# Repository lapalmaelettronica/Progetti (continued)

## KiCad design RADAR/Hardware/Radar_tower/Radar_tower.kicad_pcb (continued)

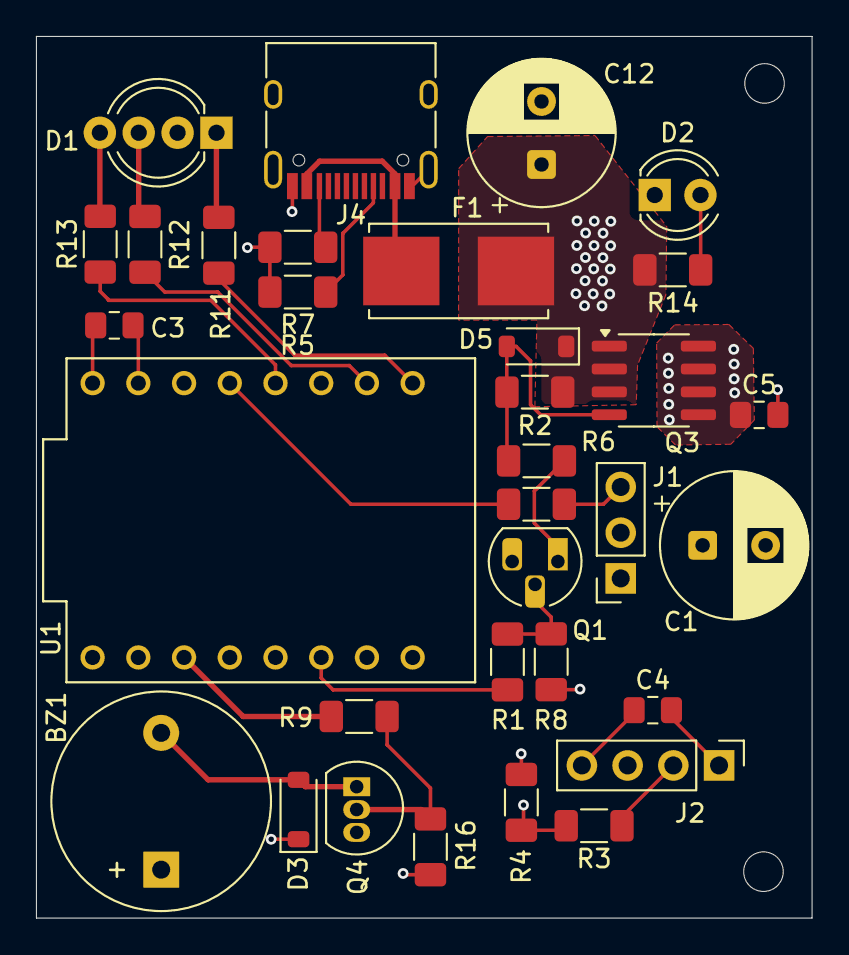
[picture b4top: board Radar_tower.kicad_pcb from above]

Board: 4 copper layers, 43.1 x 49.0 mm, 35 parts (0 on the bottom side), 25 nets.

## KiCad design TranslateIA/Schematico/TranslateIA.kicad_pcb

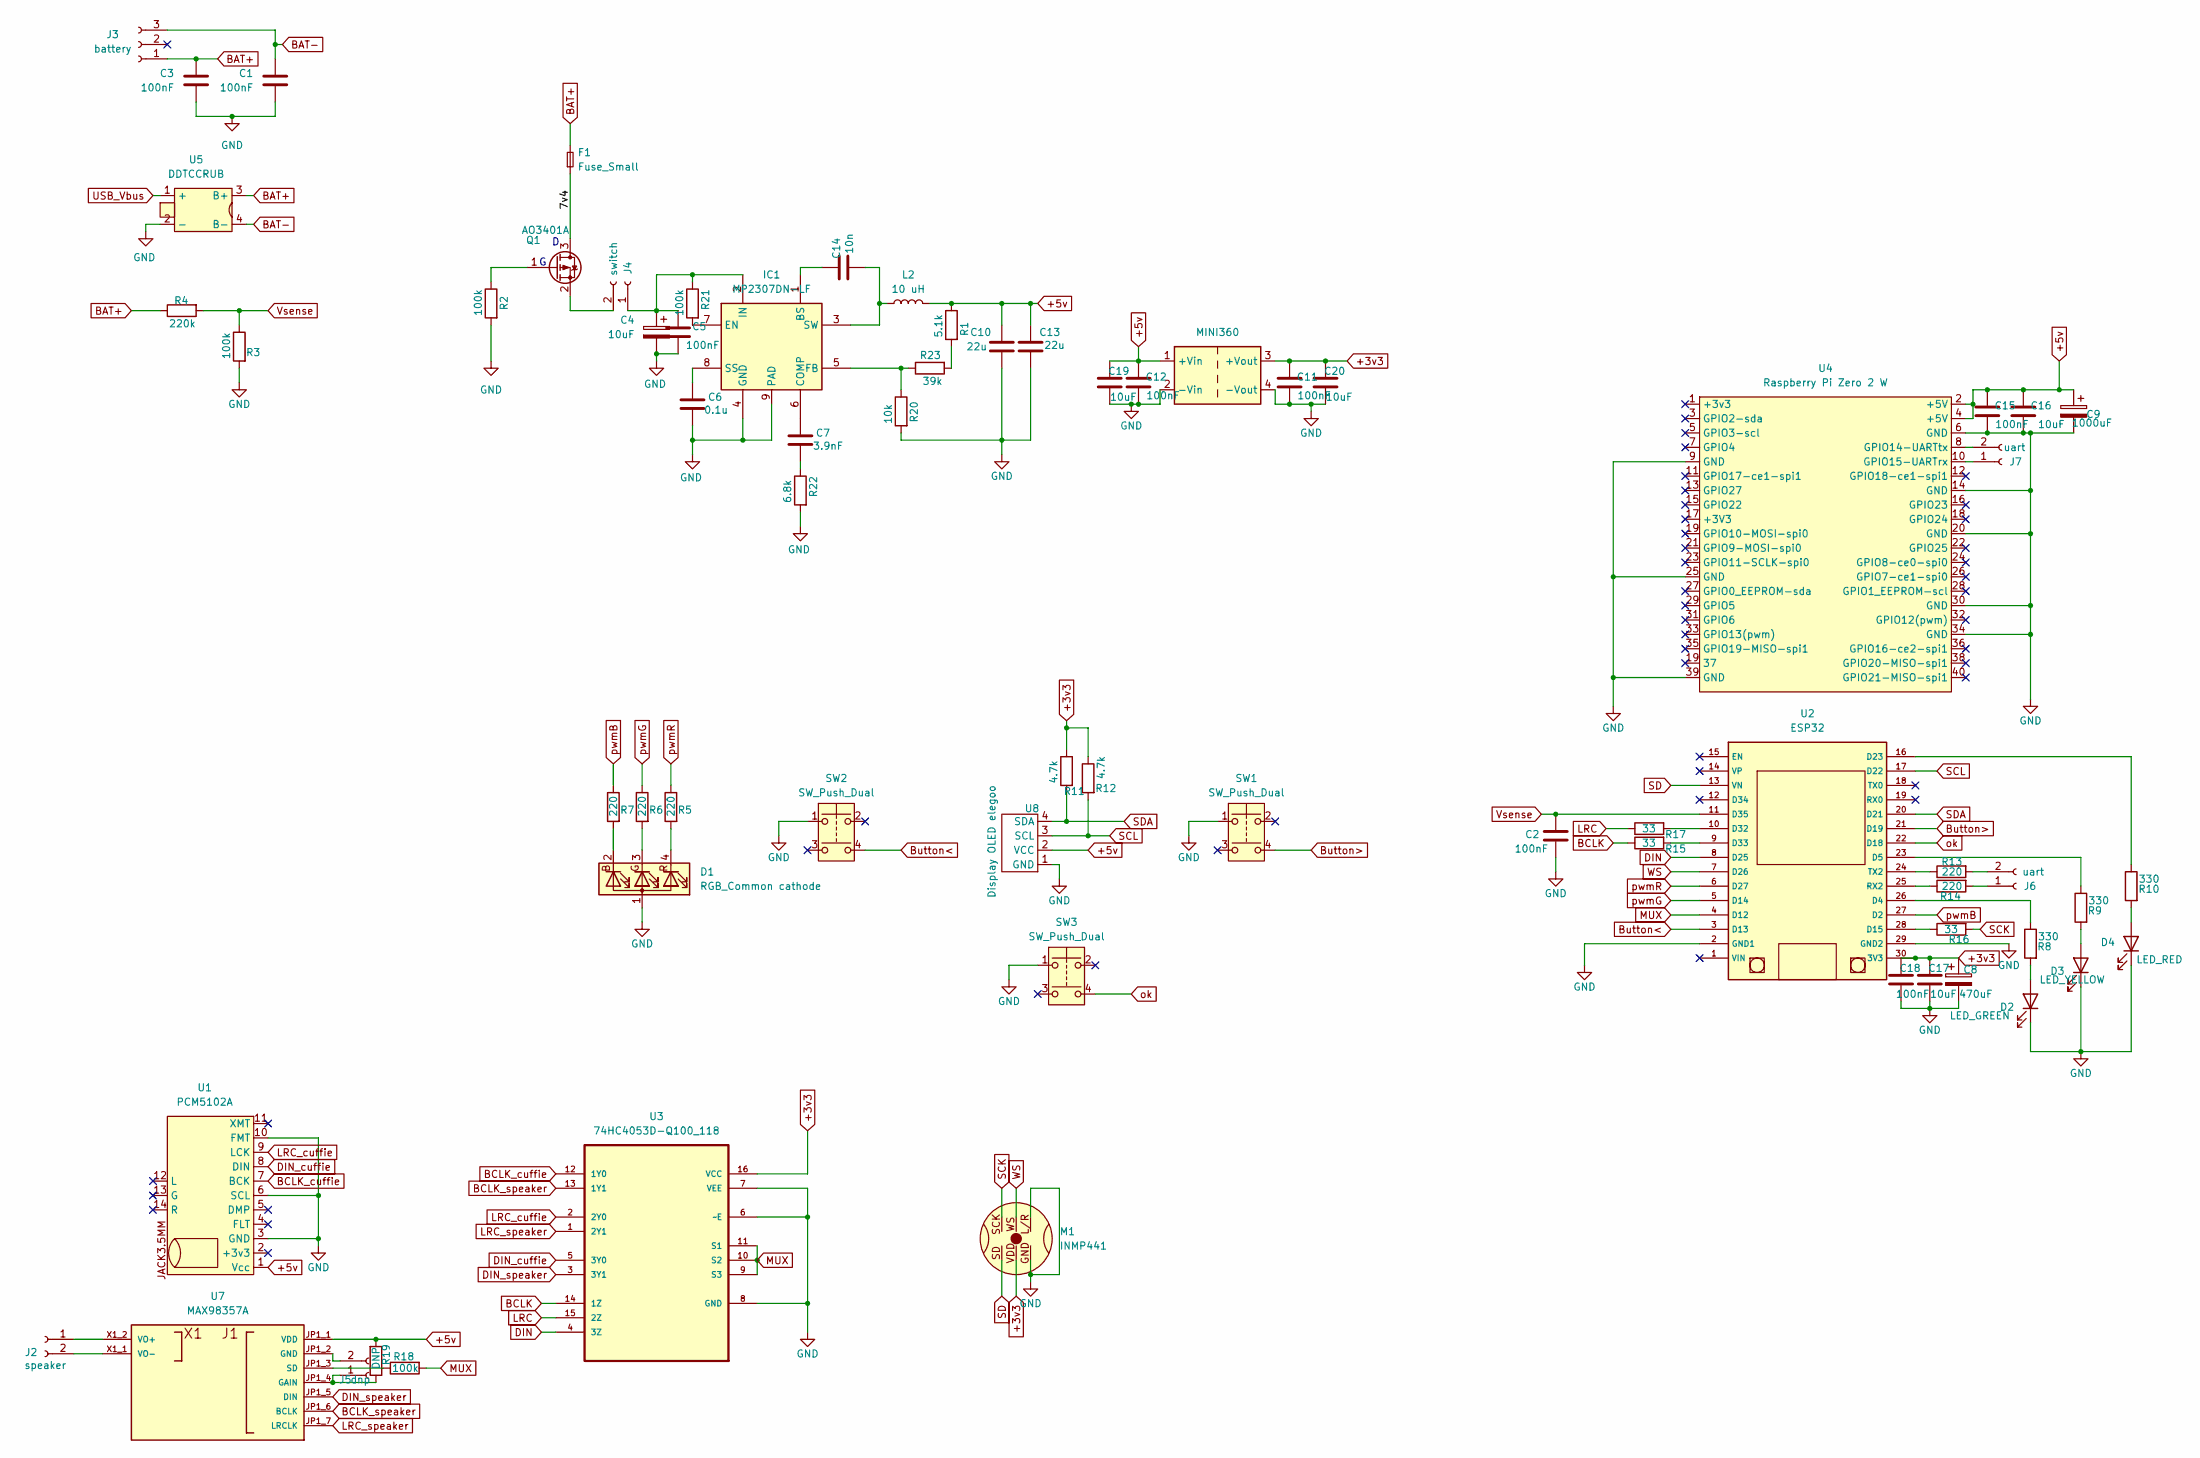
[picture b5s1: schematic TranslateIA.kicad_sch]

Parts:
C1, C2, C3, C5, C11, C12, C15, C18: 100nF; C_0805_2012Metric_Pad1.18x1.45mm_HandSolder
C4, C16, C17, C19, C20: 10uF; C_0805_2012Metric_Pad1.18x1.45mm_HandSolder
C6: 0.1u; C_Disc_D4.3mm_W1.9mm_P5.00mm
C7: 3.9nF; C_Disc_D4.3mm_W1.9mm_P5.00mm
C8: 470uF; CP_Radial_D5.0mm_P2.00mm
C9: 1000uF; CP_Radial_D5.0mm_P2.00mm
C10, C13: 22u; C_Disc_D4.3mm_W1.9mm_P5.00mm
C14: 10n; C_0805_2012Metric_Pad1.18x1.45mm_HandSolder
D1: RGB_Common cathode; LED_D5.0mm-4_RGB_Wide_Pins
D2: LED_GREEN; LED_D4.0mm
D3: LED_YELLOW; LED_D4.0mm
D4: LED_RED; LED_D4.0mm
F1: Fuse_Small; Fuseholder_Littelfuse_Nano2_154x
IC1: MP2307DN-LF; MP2307DNLF; Mouser Part Number 946-MP2307DNLF
J2: speaker; JST_PH_B2B-PH-K_1x02_P2.00mm_Vertical
J3: battery; JST_PH_B3B-PH-K_1x03_P2.00mm_Vertical
J4: switch; Molex_KK-254_AE-6410-02A_1x02_P2.54mm_Vertical
J5: dnp; Molex_KK-254_AE-6410-02A_1x02_P2.54mm_Vertical
J6, J7: uart; Molex_KK-254_AE-6410-02A_1x02_P2.54mm_Vertical
L2: 10 uH; CDRH127
M1: INMP441
Q1: AO3401A; SOT-23
R1: 5.1k; R_1206_3216Metric_Pad1.30x1.75mm_HandSolder
R2, R3, R18, R21: 100k; R_1206_3216Metric_Pad1.30x1.75mm_HandSolder
R4: 220k; R_1206_3216Metric_Pad1.30x1.75mm_HandSolder
R5, R6, R7, R13, R14: 220; R_1206_3216Metric_Pad1.30x1.75mm_HandSolder
R8, R9, R10: 330; R_1206_3216Metric_Pad1.30x1.75mm_HandSolder
R11, R12: 4.7k; R_1206_3216Metric_Pad1.30x1.75mm_HandSolder
R15, R16, R17: 33; R_1206_3216Metric_Pad1.30x1.75mm_HandSolder
R19: DNP; R_1206_3216Metric_Pad1.30x1.75mm_HandSolder
R20: 10k; R_1206_3216Metric_Pad1.30x1.75mm_HandSolder
R22: 6.8k; R_1206_3216Metric_Pad1.30x1.75mm_HandSolder
R23: 39k; R_1206_3216Metric_Pad1.30x1.75mm_HandSolder
SW1, SW2, SW3: SW_Push_Dual; Push_E-Switch_KS01Q01
U1: PCM5102A
U2: ESP32
U3: 74HC4053D-Q100_118; 74HC4053D-SOIC16; MPN 74HC4053D-Q100,118
U4: Raspberry Pi Zero 2 W; Raspberry_Pi_Zero_Socketed_THT_FaceDown_MountingHoles
U5: DDTCCRUB; DDTCCRUB lithium battery charger
U6: MINI360; Mini360
U7: MAX98357A; PARTREV A
U8: Display OLED elegoo; Display OLED mini Elegoo

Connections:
+3v3: C8.1, C11.1, C17.1, C18.1, C20.1, M1.VDD, R11.1, R12.1, U2.30 (3V3), U3.16 (VCC), U6.3 (+Vout)
+5v: C9.1, C10.1, C12.1, C13.1, C15.1, C16.1, C19.1, L2.2, R1.1, R19.2, U1.1 (Vcc), U4.2 (+5V), U4.4 (+5V), U6.1 (+Vin), U7.JP1_1 (VDD), U8.2 (VCC)
/7v4: F1.1, Q1.3 (D)
BAT+: C3.1, F1.2, J3.1, R4.1, U5.3 (B+)
BAT-: C1.1, J3.3, U5.4 (B-)
BCLK: R15.1, U3.14 (1Z)
BCLK_cuffie: U1.7 (BCK), U3.12 (1Y0)
BCLK_speaker: U3.13 (1Y1), U7.JP1_6 (BCLK)
Button<: SW2.4, U2.3 (D13)
Button>: SW1.4, U2.21 (D19)
DIN: U2.8 (D25), U3.4 (3Z)
DIN_cuffie: U1.8 (DIN), U3.5 (3Y0)
DIN_speaker: U3.3 (3Y1), U7.JP1_5 (DIN)
GND: C1.2, C2.2, C3.2, C4.2, C5.2, C6.2, C8.2, C9.2, C10.2, C11.2, C12.2, C13.2, C15.2, C16.2, C17.2, C18.2, C19.2, C20.2, D1.1 (A), D2.1 (K), D3.1 (K), D4.1 (K), IC1.4 (GND), IC1.9 (PAD), M1.GND, M1.L/R, R2.2, R3.2, R20.2, R22.2, SW1.1, SW2.1, SW3.1, U1.3 (GND), U1.6 (SCL), U1.10 (FMT), U2.2 (GND1), U2.29 (GND2), U3.6 (~E), U3.7 (VEE), U3.8 (GND), U4.6 (GND), U4.9 (GND), U4.14 (GND), U4.20 (GND), U4.25 (GND), U4.30 (GND), U4.34 (GND), U4.39 (GND), U5.2 (-), U6.2 (-Vin), U6.4 (-Vout), U8.1 (GND)
LRC: R17.1, U3.15 (2Z)
LRC_cuffie: U1.9 (LCK), U3.2 (2Y0)
LRC_speaker: U3.1 (2Y1), U7.JP1_7 (LRCLK)
MUX: R18.2, U2.4 (D12), U3.9 (S3), U3.10 (S2), U3.11 (S1)
unnamed: C7.2, R22.1
unnamed: D1.2 (BK), R7.2
unnamed: D1.3 (GK), R6.2
unnamed: D1.4 (RK), R5.2
unnamed: D2.2 (A), R8.2
unnamed: D3.2 (A), R9.2
unnamed: D4.2 (A), R10.2
unnamed: C14.1, IC1.1 (BS)
unnamed: C7.1, IC1.6 (COMP)
unnamed: IC1.7 (EN), R21.2
unnamed: IC1.5 (FB), R20.1, R23.1
unnamed: C4.1, C5.1, IC1.2 (IN), J4.1, R21.1
unnamed: C6.1, IC1.8 (SS)
unnamed: C14.2, IC1.3 (SW), L2.1
unnamed: J2.1, U7.X1_2 (VO+)
unnamed: J2.2, U7.X1_1 (VO-)
unnamed: J4.2, Q1.2 (S)
unnamed: J5.1, R19.1, U7.JP1_4 (GAIN)
unnamed: J5.2, U7.JP1_2 (GND)
unnamed: J6.1, R14.2
unnamed: J6.2, R13.2
unnamed: J7.1, U4.10 (GPIO15-UARTrx)
unnamed: J7.2, U4.8 (GPIO14-UARTtx)
unnamed: Q1.1 (G), R2.1
unnamed: R1.2, R23.2
unnamed: R8.1, U2.26 (D4)
unnamed: R9.1, U2.23 (D5)
unnamed: R16.1, U2.28 (D15)
unnamed: R10.1, U2.16 (D23)
unnamed: R17.2, U2.10 (D32)
unnamed: R15.2, U2.9 (D33)
unnamed: R14.1, U2.25 (RX2)
unnamed: R13.1, U2.24 (TX2)
unnamed: R18.1, U7.JP1_3 (SD)
SCK: M1.SCK, R16.2
SCL: R12.2, U2.17 (D22), U8.3 (SCL)
SD: M1.SD, U2.13 (VN)
SDA: R11.2, U2.20 (D21), U8.4 (SDA)
USB_Vbus: U5.1 (+)
Vsense: C2.1, R3.1, R4.2, U2.11 (D35)
WS: M1.WS, U2.7 (D26)
ok: SW3.4, U2.22 (D18)
pwmB: R7.1, U2.27 (D2)
pwmG: R6.1, U2.5 (D14)
pwmR: R5.1, U2.6 (D27)

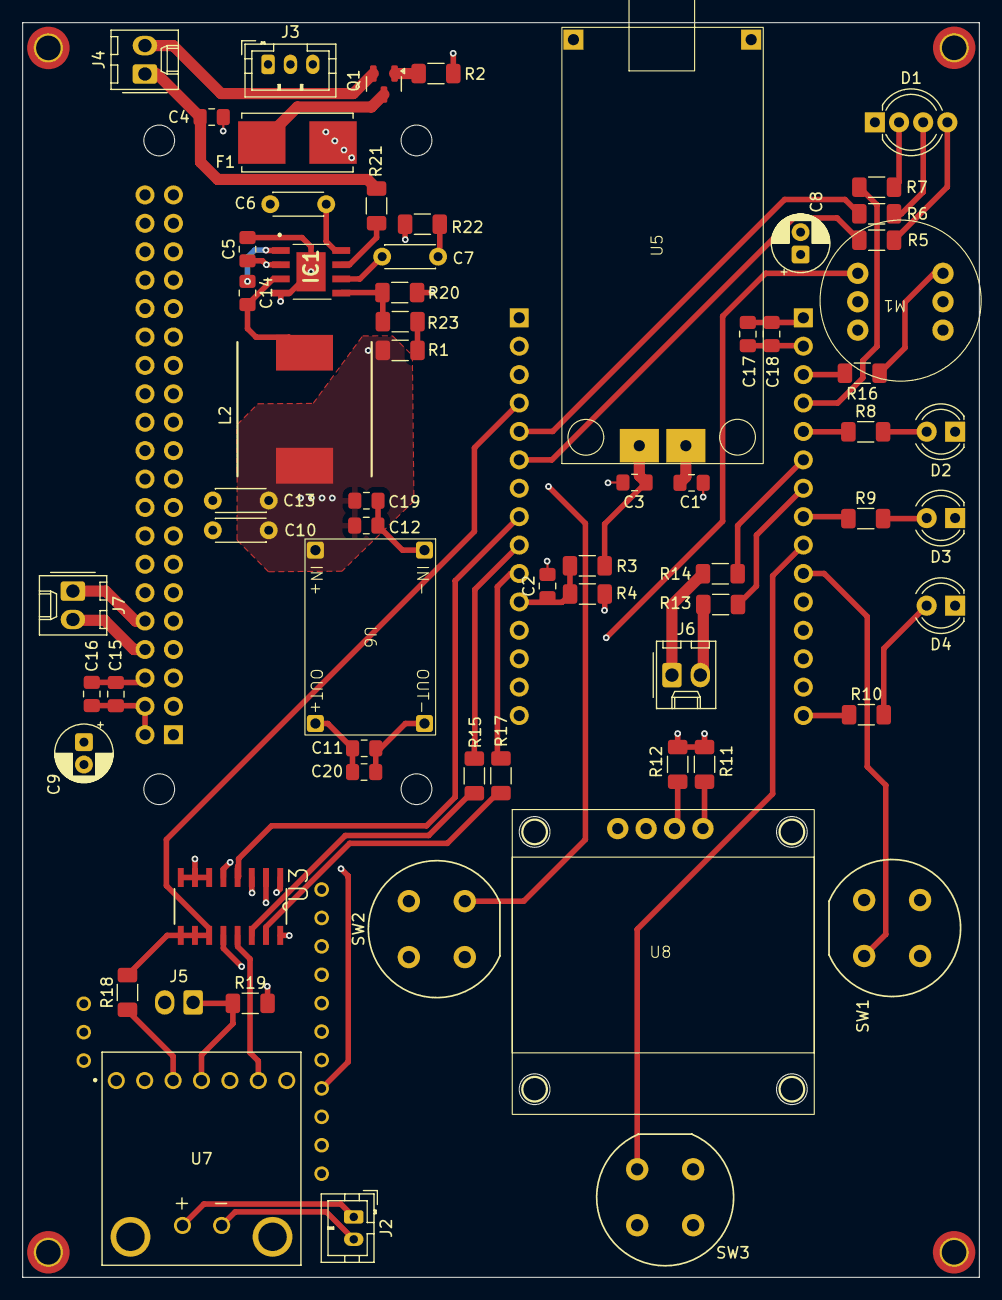
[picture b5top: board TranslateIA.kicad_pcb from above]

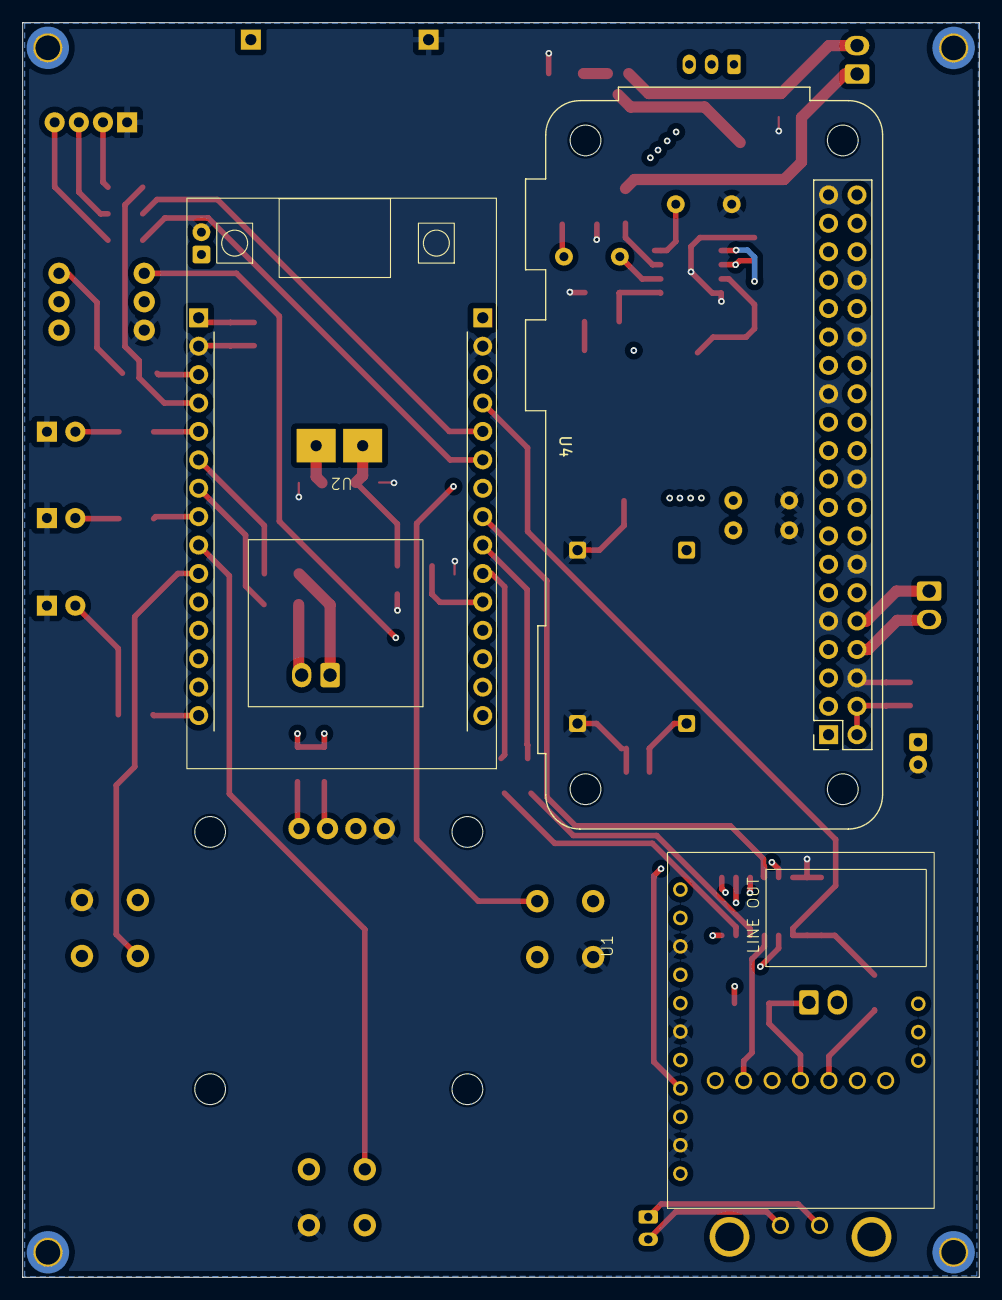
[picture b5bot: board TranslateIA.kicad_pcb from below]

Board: 4 copper layers, 85.5 x 112.2 mm, 69 parts (3 on the bottom side), 62 nets.

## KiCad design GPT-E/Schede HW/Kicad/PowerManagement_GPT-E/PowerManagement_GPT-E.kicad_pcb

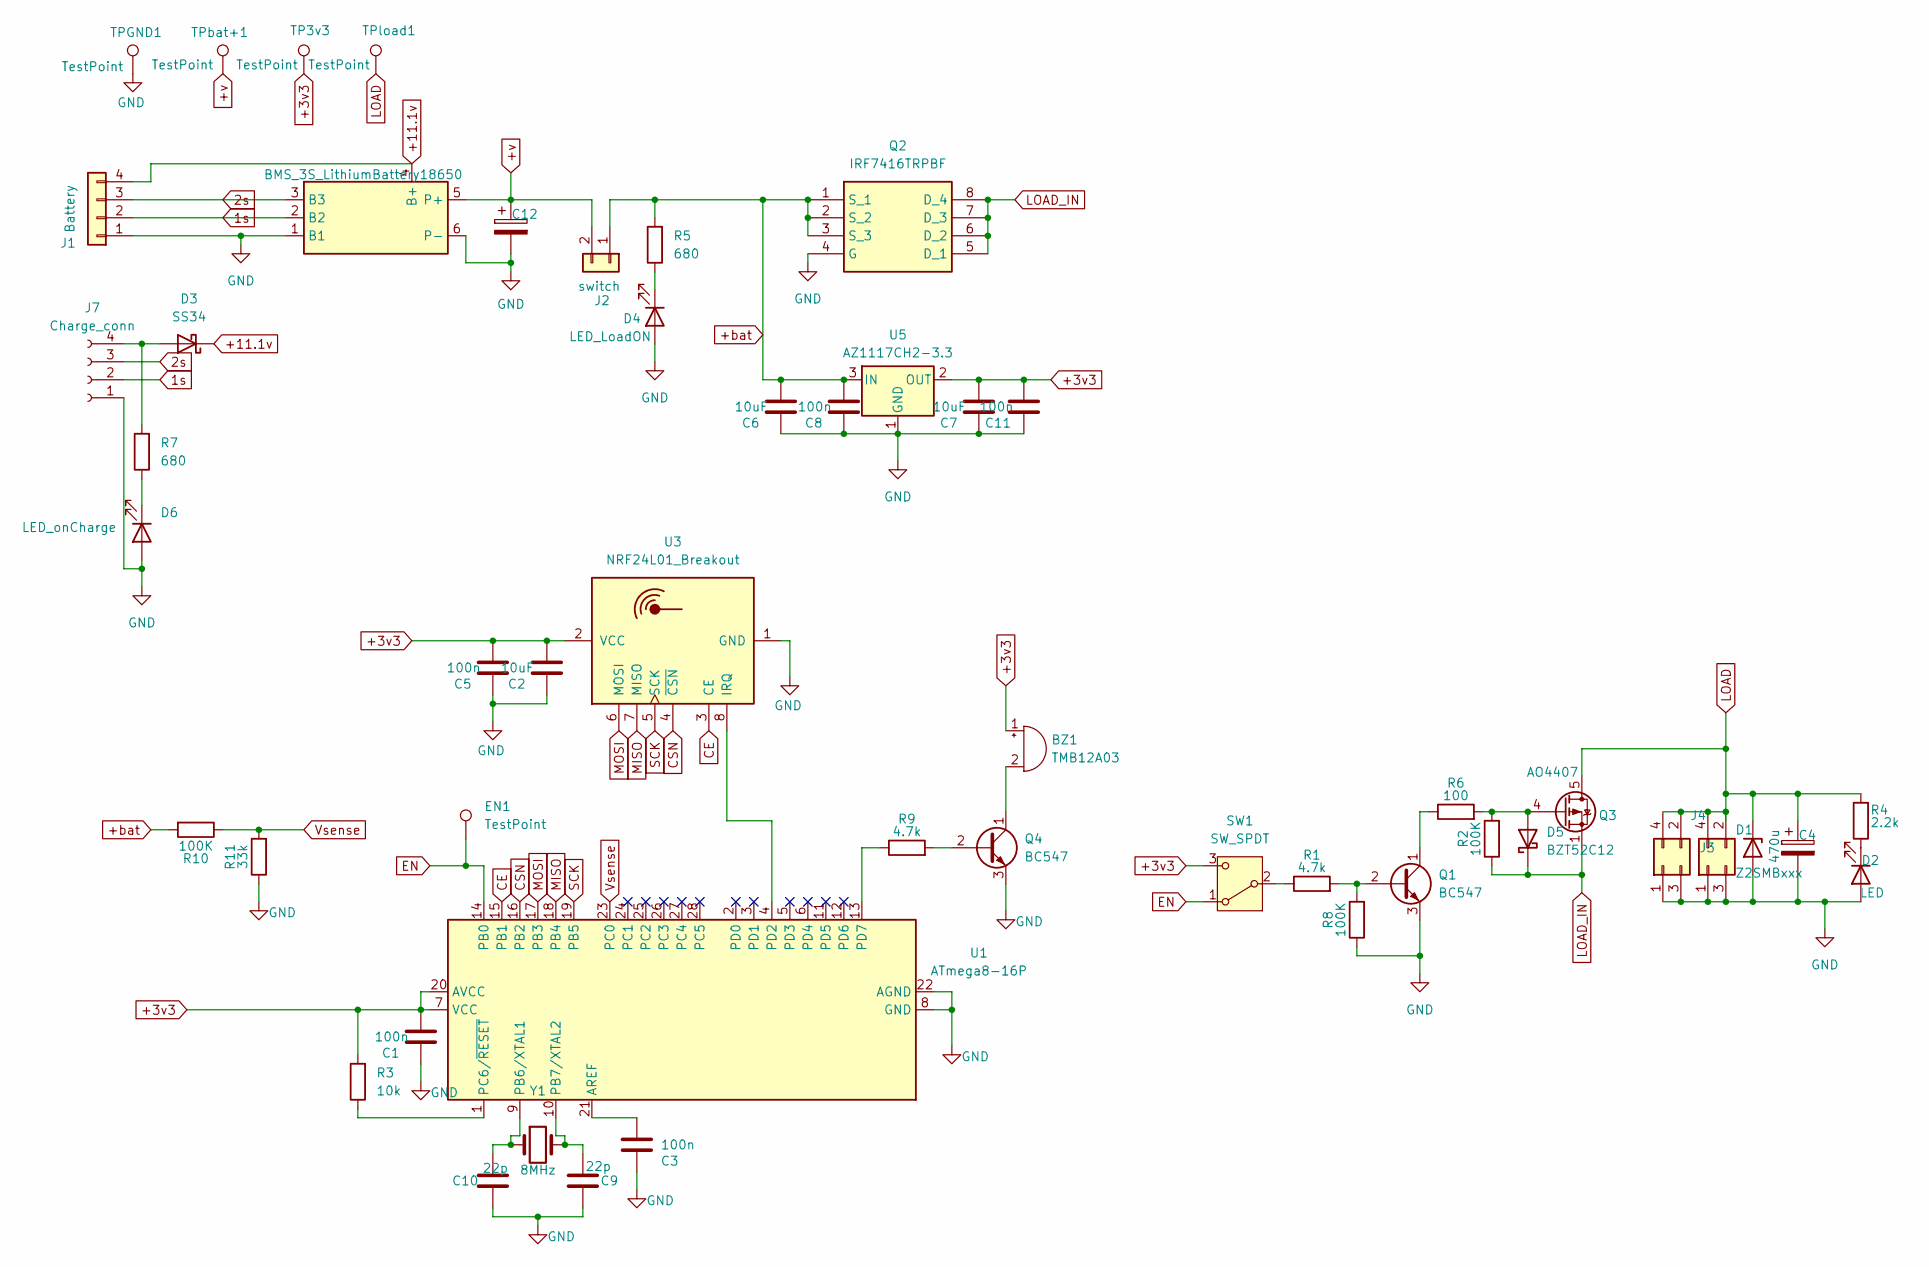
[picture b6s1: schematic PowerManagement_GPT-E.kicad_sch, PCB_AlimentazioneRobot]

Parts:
BZ1: TMB12A03; Buzzer_12x9.5RM7.6
C1, C3, C5, C8, C11: 100n; C_0805_2012Metric_Pad1.18x1.45mm_HandSolder
C2, C6, C7: 10uF; C_0805_2012Metric_Pad1.18x1.45mm_HandSolder
C4, C12: 470u; CP_Radial_D8.0mm_P3.50mm
C9, C10: 22p; C_0805_2012Metric_Pad1.18x1.45mm_HandSolder
D1: Z2SMBxxx; D_SMB_Handsoldering
D2: LED; LED_D4.0mm
D3: SS34; D_SMA_Handsoldering
D4: LED_LoadON; LED_D4.0mm
D5: BZT52C12; D_SOD-123
D6: LED_onCharge; LED_D4.0mm
EN1: TestPoint; TestPoint_Pad_2.0x2.0mm
J1: Battery; FanPinHeader_1x04_P2.54mm_Vertical
J2: switch; Molex_KK-254_AE-6410-02A_1x02_P2.54mm_Vertical
J3: Conn_02x02_Counter_Clockwise; Molex_Micro-Fit_3.0_43045-0412_2x02_P3.00mm_Vertical
J4: Conn_02x02_Counter_Clockwise; Molex_Micro-Fit_3.0_43045-0400_2x02_P3.00mm_Horizontal
J7: Charge_conn; Samtec_UMPS-04-XX.X-X-V-S_1x04_P2.0mm_Socket
Q1, Q4: BC547; TO-92L_Inline
Q2: IRF7416TRPBF; SOIC-8; Mouser Part Number 942-IRF7416TRPBF
Q3: AO4407; SOIC-8_3.9x4.9mm_P1.27mm
R1, R9: 4.7k; R_1206_3216Metric_Pad1.30x1.75mm_HandSolder
R2, R8: 100K; R_1206_3216Metric_Pad1.30x1.75mm_HandSolder
R3: 10k; R_Axial_DIN0204_L3.6mm_D1.6mm_P5.08mm_Horizontal
R4: 2.2k; R_Axial_DIN0204_L3.6mm_D1.6mm_P5.08mm_Horizontal
R5, R7: 680; R_Axial_DIN0204_L3.6mm_D1.6mm_P5.08mm_Horizontal
R6: 100; R_1206_3216Metric_Pad1.30x1.75mm_HandSolder
R10: 100K; R_Axial_DIN0204_L3.6mm_D1.6mm_P5.08mm_Horizontal
R11: 33k; R_Axial_DIN0204_L3.6mm_D1.6mm_P5.08mm_Horizontal
SW1: SW_SPDT; PinSocket_1x03_P2.54mm_Vertical
TP3v3: TestPoint; TestPoint_Pad_2.0x2.0mm
TPGND1: TestPoint; TestPoint_Pad_2.0x2.0mm
TPbat+1: TestPoint; TestPoint_Pad_2.0x2.0mm
TPload1: TestPoint; TestPoint_Pad_2.0x2.0mm
U1: ATmega8-16P; DIP-28_W7.62mm
U2: BMS_3S_LithiumBattery18650; BMS-4S
U3: NRF24L01_Breakout; nRF24L01_Breakout
U5: AZ1117CH2-3.3; SOT-223-3_TabPin2
Y1: 8MHz; Crystal_HC18-U_Vertical

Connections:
1s: J1.2, J7.2, U2.2 (B2)
2s: J1.3, J7.3, U2.3 (B3)
+3v3: BZ1.1 (+), C1.1, C2.1, C5.1, C7.1, C11.1, R3.2, SW1.3 (C), TP3v3.1, U1.7 (VCC), U1.20 (AVCC), U3.2 (VCC), U5.2 (OUT)
+11.1v: D3.1 (K), J1.4, U2.4 (B+)
+bat: C6.1, C8.1, J2.1, Q2.1 (S_1), Q2.2 (S_2), Q2.3 (S_3), R5.2, R10.2, U5.3 (IN)
+v: C12.1, J2.2, TPbat+1.1, U2.5 (P+)
CE: U1.15 (PB1), U3.3 (CE)
CSN: U1.16 (PB2), U3.4 (~CSN)
EN: EN1.1, SW1.1 (A), U1.14 (PB0)
GND: C1.2, C2.2, C3.2, C4.2, C5.2, C6.2, C7.2, C8.2, C9.1, C10.2, C11.2, C12.2, D1.2 (A), D2.2 (A), D4.2 (A), D6.2 (A), J1.1, J3.1, J3.3, J4.1, J4.3, J7.1, Q1.3 (E), Q2.4 (G), Q4.3 (E), R8.1, R11.1, TPGND1.1, U1.8 (GND), U1.22 (AGND), U2.1 (B1), U2.6 (P-), U3.1 (GND), U5.1 (GND)
LOAD: C4.1, D1.1 (K), J3.2, J3.4, J4.2, J4.4, Q3.5 (D), Q3.6 (D), Q3.7 (D), Q3.8 (D), R4.2, TPload1.1
LOAD_IN: D5.1 (K), Q2.5 (D_1), Q2.6 (D_2), Q2.7 (D_3), Q2.8 (D_4), Q3.1 (S), Q3.2 (S), Q3.3 (S), R2.1
MISO: U1.18 (PB4), U3.7 (MISO)
MOSI: U1.17 (PB3), U3.6 (MOSI)
unnamed: BZ1.2 (-), Q4.1 (C)
unnamed: D2.1 (K), R4.1
unnamed: D3.2 (A), J7.4, R7.2
unnamed: D4.1 (K), R5.1
unnamed: D5.2 (A), Q3.4 (G), R2.2, R6.2
unnamed: D6.1 (K), R7.1
unnamed: Q1.2 (B), R1.2, R8.2
unnamed: Q1.1 (C), R6.1
unnamed: Q4.2 (B), R9.2
unnamed: R1.1, SW1.2 (B)
unnamed: C3.1, U1.21 (AREF)
unnamed: C10.1, U1.9 (PB6/XTAL1), Y1.1
unnamed: C9.2, U1.10 (PB7/XTAL2), Y1.2
unnamed: R3.1, U1.1 (PC6/~RESET)
unnamed: U1.4 (PD2), U3.8 (IRQ)
unnamed: R9.1, U1.13 (PD7)
SCK: U1.19 (PB5), U3.5 (SCK)
Vsense: R10.1, R11.2, U1.23 (PC0)

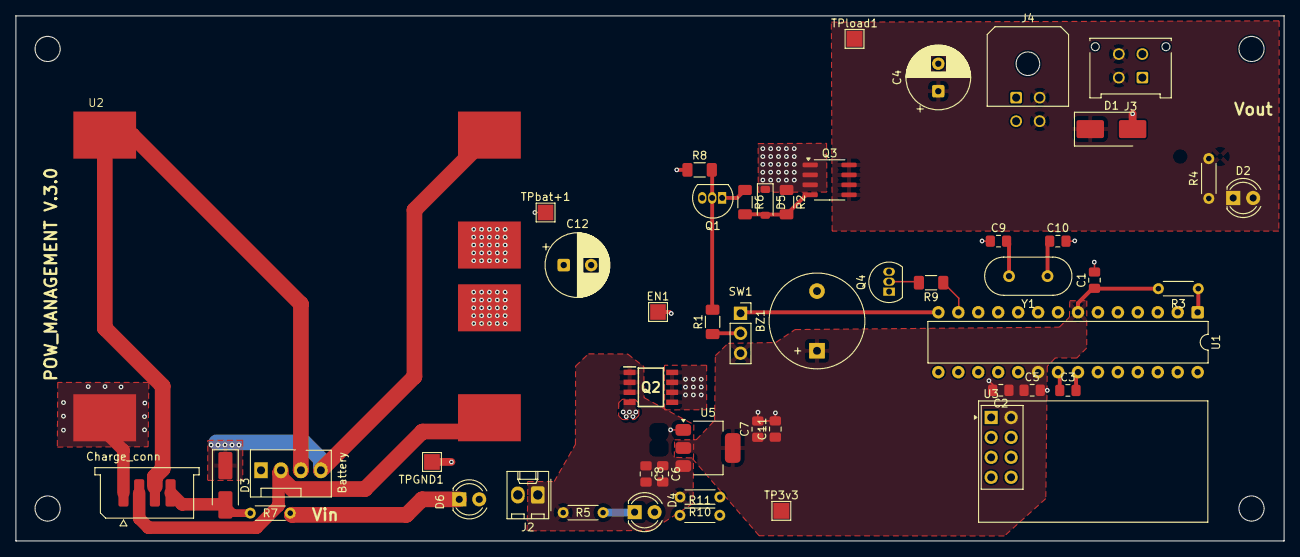
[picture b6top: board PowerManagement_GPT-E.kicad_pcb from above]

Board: 4 copper layers, 161.5 x 66.9 mm, 50 parts (0 on the bottom side), 32 nets.

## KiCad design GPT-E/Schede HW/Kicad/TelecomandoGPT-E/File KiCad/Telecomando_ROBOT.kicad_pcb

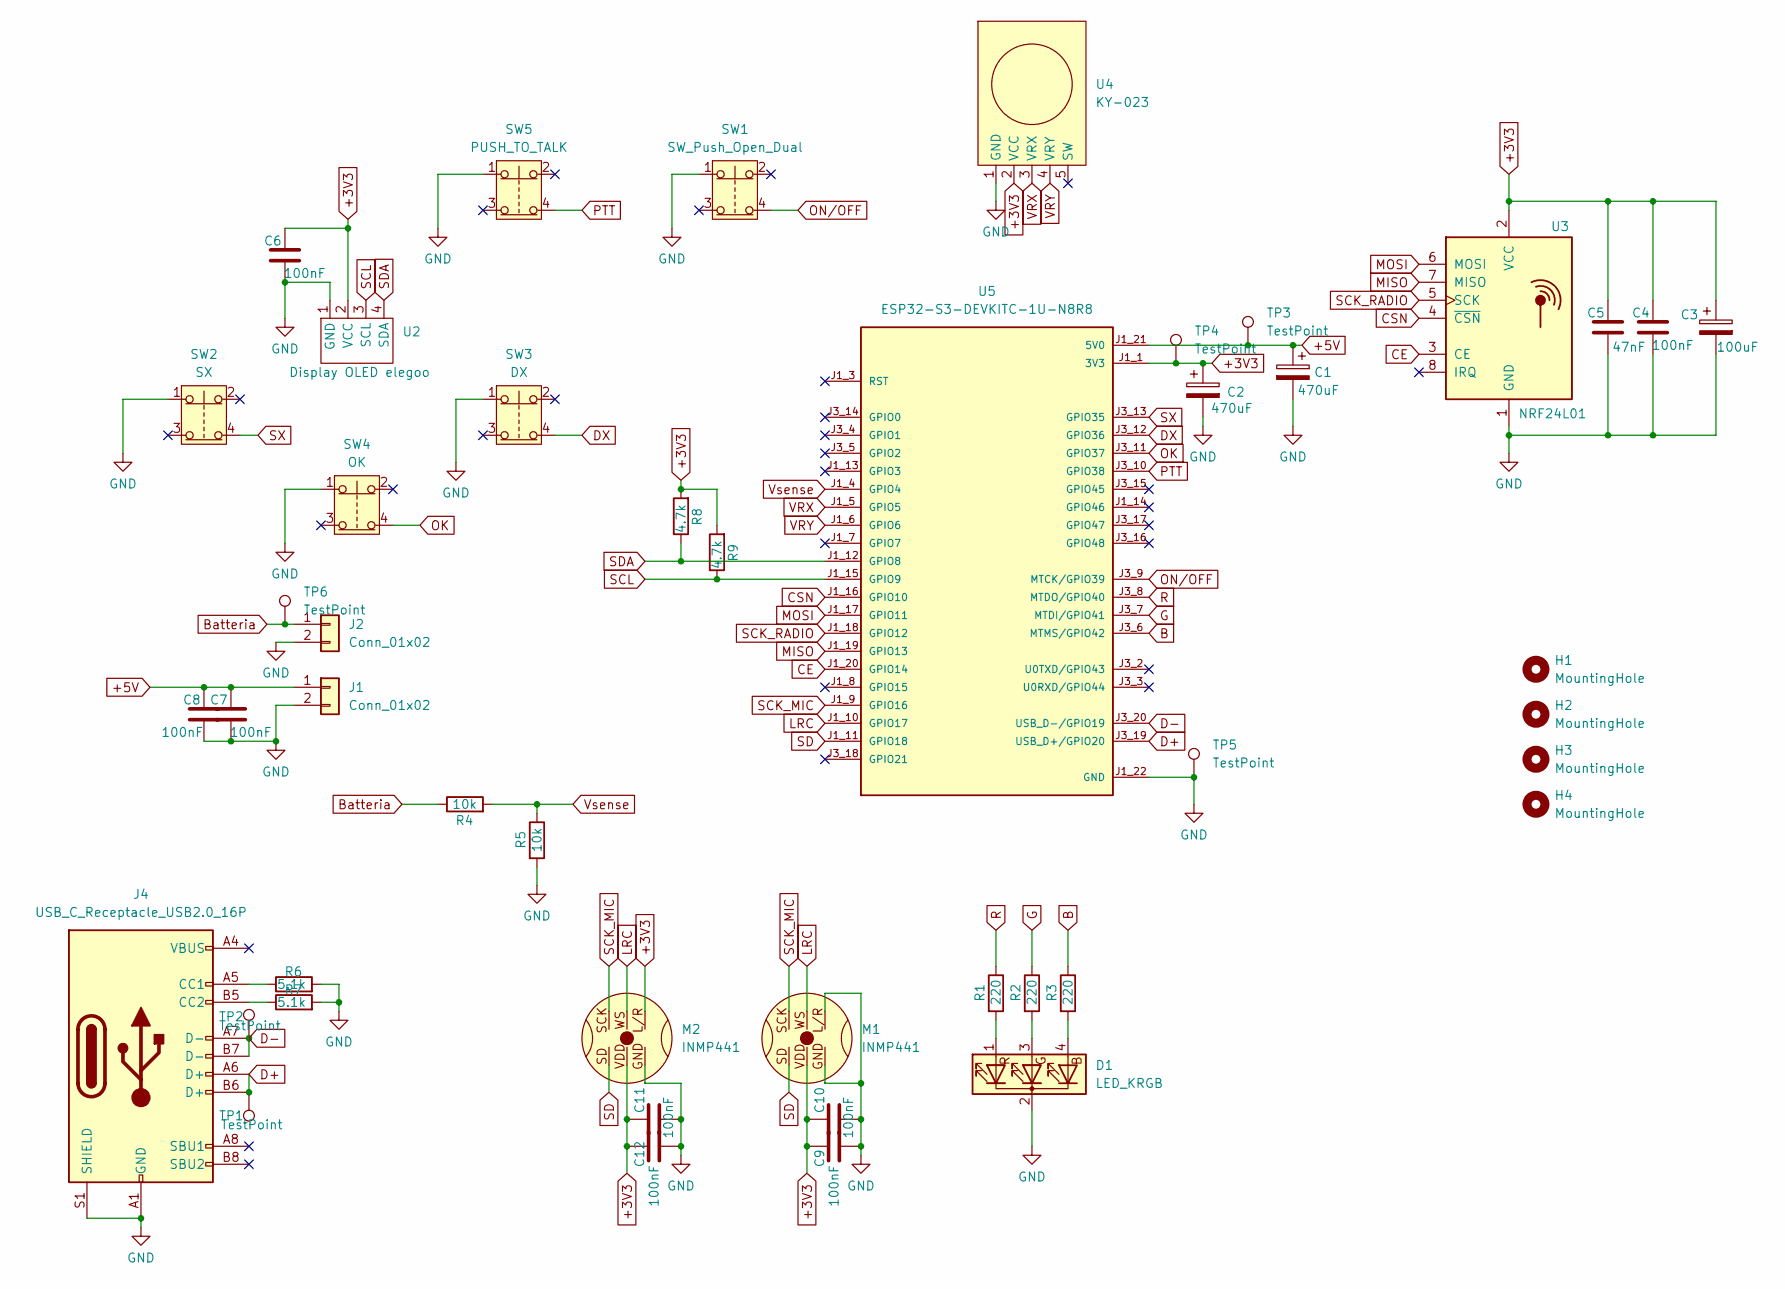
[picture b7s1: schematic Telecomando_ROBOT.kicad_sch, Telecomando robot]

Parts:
C1, C2: 470uF; CP_Radial_D5.0mm_P2.50mm
C3: 100uF; CP_Radial_D5.0mm_P2.50mm
C4, C6, C7, C8, C9, C10, C11, C12: 100nF; C_1206_3216Metric_Pad1.33x1.80mm_HandSolder
C5: 47nF; C_1206_3216Metric_Pad1.33x1.80mm_HandSolder
D1: LED_KRGB; LED_D5.0mm-4_RGB_Wide_Pins
H1, H2, H3, H4: MountingHole; MountingHole_3.2mm_M3
J1, J2: Conn_01x02; JST_EH_B2B-EH-A_1x02_P2.50mm_Vertical
J4: USB_C_Receptacle_USB2.0_16P; USB_C_Receptacle_HRO_TYPE-C-31-M-12
M1, M2: INMP441
R1, R2, R3: 220; R_1206_3216Metric_Pad1.30x1.75mm_HandSolder
R4, R5: 10k; R_1206_3216Metric_Pad1.30x1.75mm_HandSolder
R6, R7: 5.1k; R_1206_3216Metric_Pad1.30x1.75mm_HandSolder
R8, R9: 4.7k; R_1206_3216Metric_Pad1.30x1.75mm_HandSolder
SW1: SW_Push_Open_Dual; SW_PUSH_6mm_H8mm
SW2: SX; SW_PUSH_6mm_H8mm
SW3: DX; SW_PUSH_6mm_H8mm
SW4: OK; SW_PUSH_6mm_H8mm
SW5: PUSH_TO_TALK; SW_PUSH_6mm_H8mm
TP1, TP2, TP3, TP4, TP5, TP6: TestPoint; TestPoint_Pad_D1.5mm
U2: Display OLED elegoo; Display OLED mini Elegoo
U3: NRF24L01; nRF24L01_Breakout
U4: KY-023; JOYSTICK KY-023
U5: ESP32-S3-DEVKITC-1U-N8R8; MODULE_ESP32-S3-DEVKITC-1U-N8R8; PARTREV 1.1

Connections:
+3V3: C2.1, C3.1, C4.1, C5.1, C6.1, C9.1, C10.1, C11.1, C12.1, M1.VDD, M2.L/R, M2.VDD, R8.2, R9.2, TP4.1, U2.2 (VCC), U3.2 (VCC), U4.2 (VCC), U5.J1_1 (3V3), U5.J1_2 (3V3)
+5V: C1.1, C7.1, C8.1, J1.1, TP3.1, U5.J1_21 (5V0)
B: R3.1, U5.J3_6 (MTMS/GPIO42)
Batteria: J2.1, R4.1, TP6.1
CE: U3.3 (CE), U5.J1_20 (GPIO14)
CSN: U3.4 (~CSN), U5.J1_16 (GPIO10)
D+: J4.A6 (D+), J4.B6 (D+), TP1.1, U5.J3_19 (USB_D+/GPIO20)
D-: J4.A7 (D-), J4.B7 (D-), TP2.1, U5.J3_20 (USB_D-/GPIO19)
DX: SW3.4, U5.J3_12 (GPIO36)
G: R2.1, U5.J3_7 (MTDI/GPIO41)
GND: C1.2, C2.2, C3.2, C4.2, C5.2, C6.2, C7.2, C8.2, C9.2, C10.2, C11.2, C12.2, D1.2 (K), J1.2, J2.2, J4.A1 (GND), J4.A12 (GND), J4.B1 (GND), J4.B12 (GND), J4.S1 (SHIELD), M1.GND, M1.L/R, M2.GND, R5.2, R6.2, R7.2, SW1.1, SW2.1, SW3.1, SW4.1, SW5.1, TP5.1, U2.1 (GND), U3.1 (GND), U4.1 (GND), U5.J1_22 (GND), U5.J3_1 (GND), U5.J3_21 (GND), U5.J3_22 (GND)
LRC: M1.WS, M2.WS, U5.J1_10 (GPIO17)
MISO: U3.7 (MISO), U5.J1_19 (GPIO13)
MOSI: U3.6 (MOSI), U5.J1_17 (GPIO11)
unnamed: D1.4 (BA), R3.2
unnamed: D1.3 (GA), R2.2
unnamed: D1.1 (RA), R1.2
unnamed: J4.A5 (CC1), R6.1
unnamed: J4.B5 (CC2), R7.1
OK: SW4.4, U5.J3_11 (GPIO37)
ON/OFF: SW1.4, U5.J3_9 (MTCK/GPIO39)
PTT: SW5.4, U5.J3_10 (GPIO38)
R: R1.1, U5.J3_8 (MTDO/GPIO40)
SCK_MIC: M1.SCK, M2.SCK, U5.J1_9 (GPIO16)
SCK_RADIO: U3.5 (SCK), U5.J1_18 (GPIO12)
SCL: R9.1, U2.3 (SCL), U5.J1_15 (GPIO9)
SD: M1.SD, M2.SD, U5.J1_11 (GPIO18)
SDA: R8.1, U2.4 (SDA), U5.J1_12 (GPIO8)
SX: SW2.4, U5.J3_13 (GPIO35)
VRX: U4.3 (VRX), U5.J1_5 (GPIO5)
VRY: U4.4 (VRY), U5.J1_6 (GPIO6)
Vsense: R4.2, R5.1, U5.J1_4 (GPIO4)

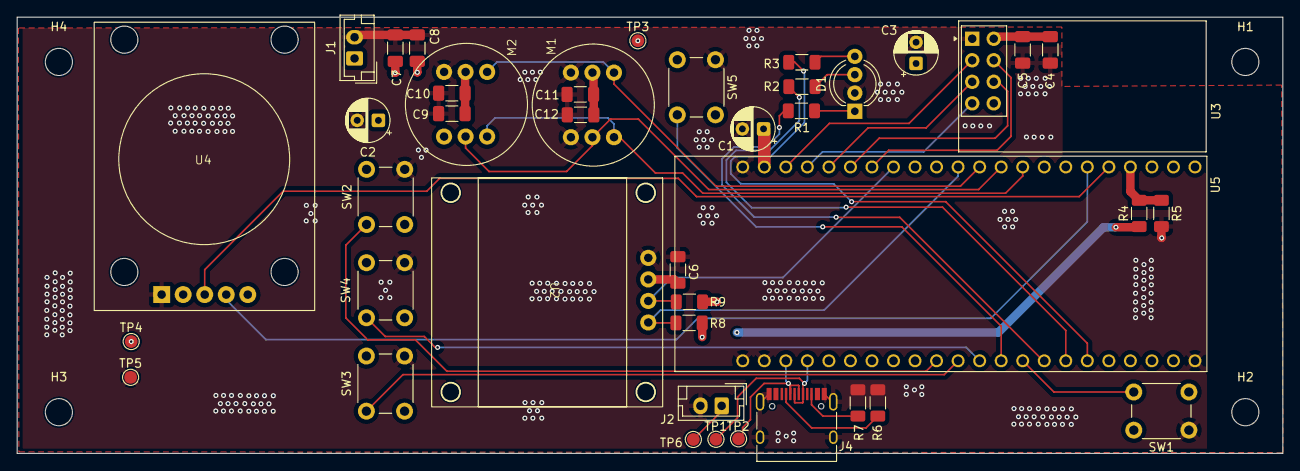
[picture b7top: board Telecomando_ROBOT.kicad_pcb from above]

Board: 4 copper layers, 149.3 x 51.5 mm, 46 parts (0 on the bottom side), 32 nets.
